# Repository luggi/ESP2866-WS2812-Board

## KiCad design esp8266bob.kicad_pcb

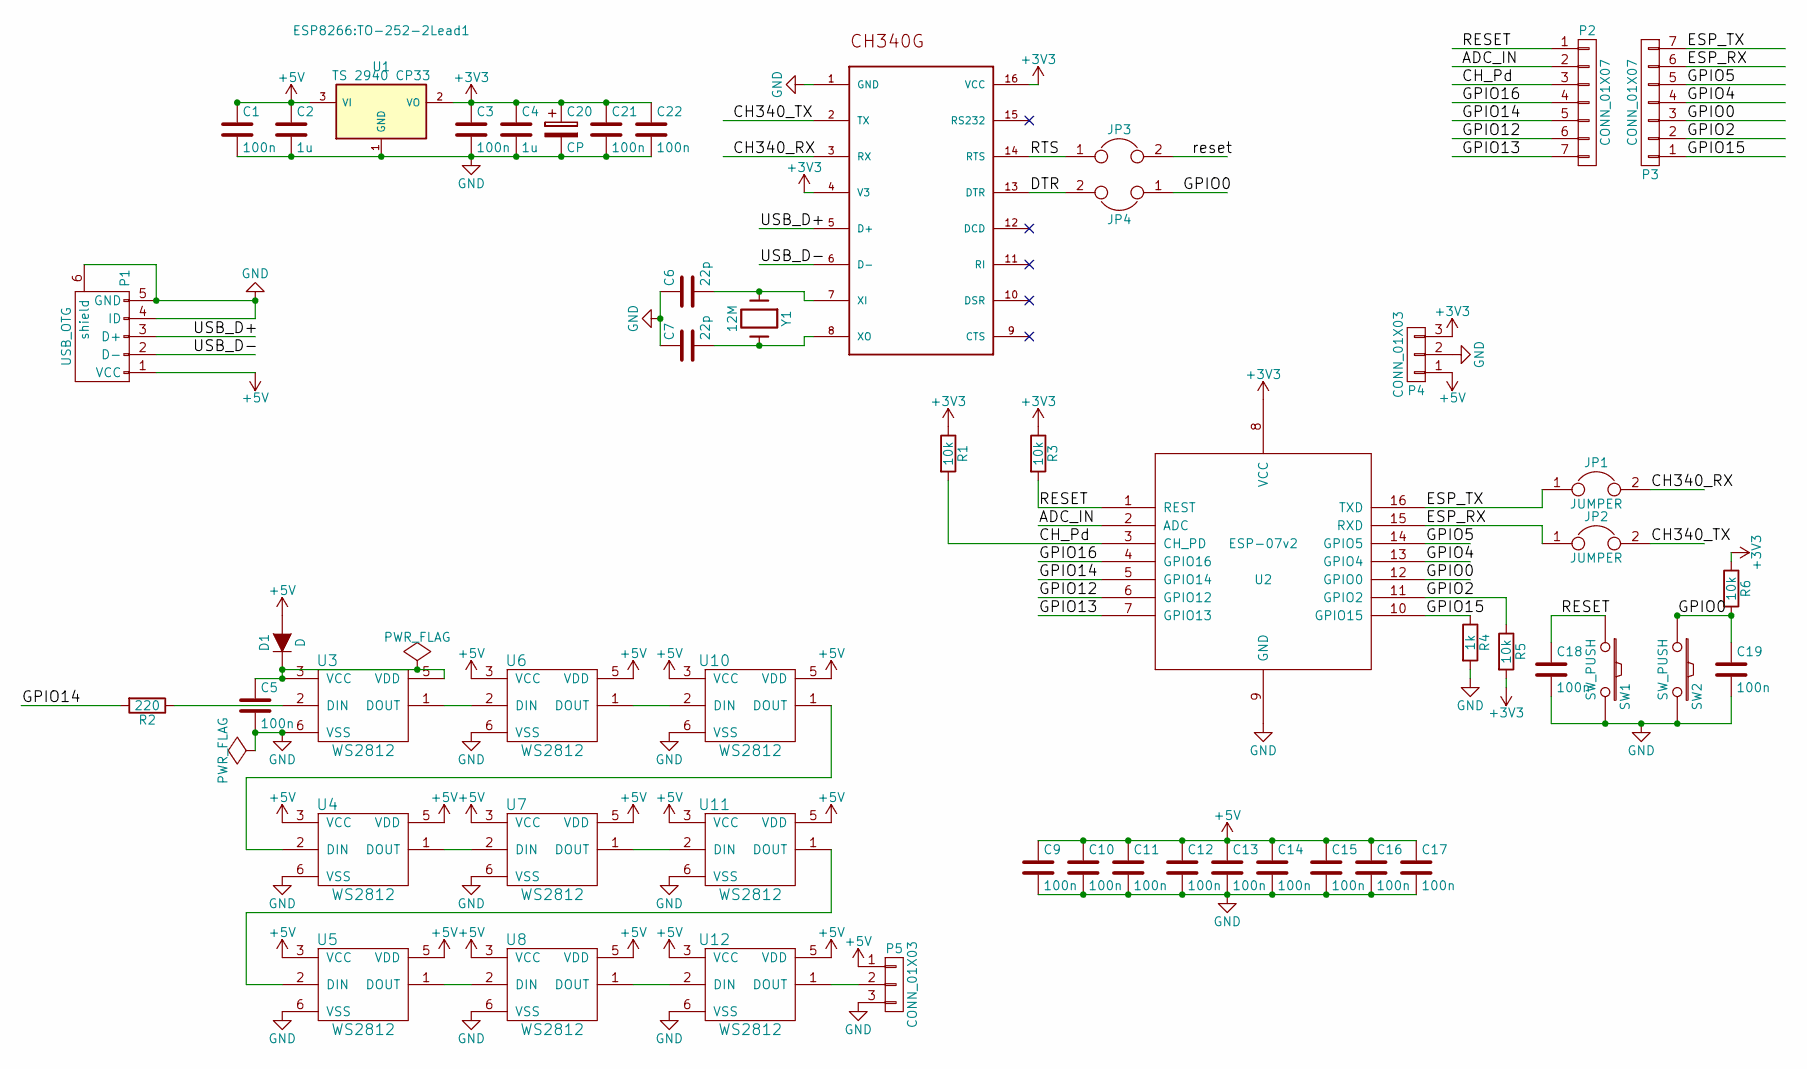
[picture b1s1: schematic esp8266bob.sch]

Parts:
C1, C3, C5, C9, C10, C11, C12, C13, C14, C15, C16, C17, C18, C19, C21, C22: 100n; C_0603_HandSoldering
C2, C4: 1u; C_0603_HandSoldering
C6, C7: 22p; C_0603_HandSoldering
C20: CP; c_elec_6.3x5.8
D1: D; MiniMELF_Handsoldering
JP1, JP2, JP3, JP4: JUMPER; S_JUMPER_2
P1: USB_OTG; USB_Micro-B
P2, P3: CONN_01X07; Pin_Header_Straight_1x07
P4, P5: CONN_01X03; Pin_Header_Straight_1x03
R1, R3, R5, R6: 10k; R_0603_HandSoldering
R2: 220; R_0603_HandSoldering
R4: 1k; R_0603_HandSoldering
SW1, SW2: SW_PUSH; SW_SPST_KMR2
U1: TS 2940 CP33; TO-252-2Lead1
U2: ESP-07v2
U3, U4, U5, U6, U7, U8, U10, U11, U12: WS2812; 5050smd
U9: CH340G; SOP-16
Y1: 12M; Crystal_HC49-U_Vertical

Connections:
+3V3: C3.1, C4.1, C20.1, C21.1, C22.1, P4.3, R1.1, R3.1, R5.2, R6.1, U1.2 (VO), U2.8 (VCC), U9.4 (V3), U9.16 (VCC)
+5V: C1.1, C2.1, C9.1, C10.1, C11.1, C12.1, C13.1, C14.1, C15.1, C16.1, C17.1, D1.2 (A), P1.1 (VCC), P4.1, P5.1, U1.3 (VI), U4.3 (VCC), U4.5 (VDD), U5.3 (VCC), U5.5 (VDD), U6.3 (VCC), U6.5 (VDD), U7.3 (VCC), U7.5 (VDD), U8.3 (VCC), U8.5 (VDD), U10.3 (VCC), U10.5 (VDD), U11.3 (VCC), U11.5 (VDD), U12.3 (VCC), U12.5 (VDD)
/ADC_IN: P2.2, U2.2 (ADC)
/CH340_RX: JP1.2, U9.3 (RX)
/CH340_TX: JP2.2, U9.2 (TX)
/CH_Pd: P2.3, R1.2, U2.3 (CH_PD)
/DTR: JP4.2, U9.13 (DTR)
/ESP_RX: JP2.1, P3.6, U2.15 (RXD)
/ESP_TX: JP1.1, P3.7, U2.16 (TXD)
/GPIO0: C19.1, JP4.1, P3.3, R6.2, SW2.1, U2.12 (GPIO0); also elsewhere on the board
/GPIO2: P3.2, R5.1, U2.11 (GPIO2)
/GPIO4: P3.4, U2.13 (GPIO4)
/GPIO5: P3.5, U2.14 (GPIO5)
/GPIO12: P2.6, U2.6 (GPIO12)
/GPIO13: P2.7, U2.7 (GPIO13)
/GPIO14: P2.5, R2.2, U2.5 (GPIO14)
/GPIO15: P3.1, R4.1, U2.10 (GPIO15)
/GPIO16: P2.4, U2.4 (GPIO16)
/RESET: C18.1, JP3.2, P2.1, R3.2, SW1.1, U2.1 (REST); also elsewhere on the board
/RTS: JP3.1, U9.14 (RTS)
/USB_D+: P1.3 (D+), U9.5 (D+)
/USB_D-: P1.2 (D-), U9.6 (D-)
GND: C1.2, C2.2, C3.2, C4.2, C5.2, C6.1, C7.1, C9.2, C10.2, C11.2, C12.2, C13.2, C14.2, C15.2, C16.2, C17.2, C18.2, C19.2, C20.2, C21.2, C22.2, P1.4 (ID), P1.5 (GND), P1.6 (shield), P4.2, P5.3, R4.2, SW1.2, SW2.2, U1.1 (GND), U2.9 (GND), U3.6 (VSS), U4.6 (VSS), U5.6 (VSS), U6.6 (VSS), U7.6 (VSS), U8.6 (VSS), U9.1 (GND), U10.6 (VSS), U11.6 (VSS), U12.6 (VSS); also elsewhere on the board
unnamed: C5.1, D1.1 (K), U3.3 (VCC), U3.5 (VDD)
unnamed: C6.2, U9.7 (XI), Y1.1
unnamed: C7.2, U9.8 (XO), Y1.2
unnamed: P5.2, U12.1 (DOUT)
unnamed: R2.1, U3.2 (DIN)
unnamed: U3.1 (DOUT), U6.2 (DIN)
unnamed: U4.1 (DOUT), U7.2 (DIN)
unnamed: U5.1 (DOUT), U8.2 (DIN)
unnamed: U4.2 (DIN), U10.1 (DOUT)
unnamed: U6.1 (DOUT), U10.2 (DIN)
unnamed: U5.2 (DIN), U11.1 (DOUT)
unnamed: U7.1 (DOUT), U11.2 (DIN)
unnamed: U8.1 (DOUT), U12.2 (DIN)

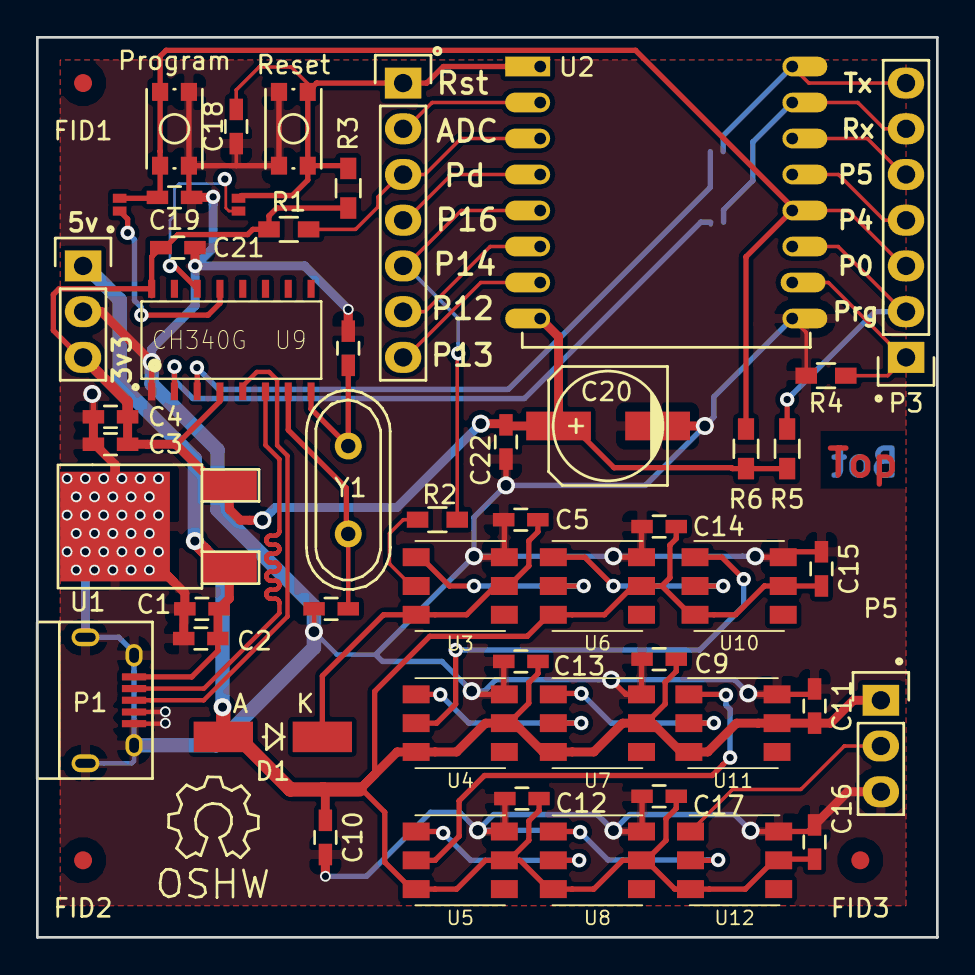
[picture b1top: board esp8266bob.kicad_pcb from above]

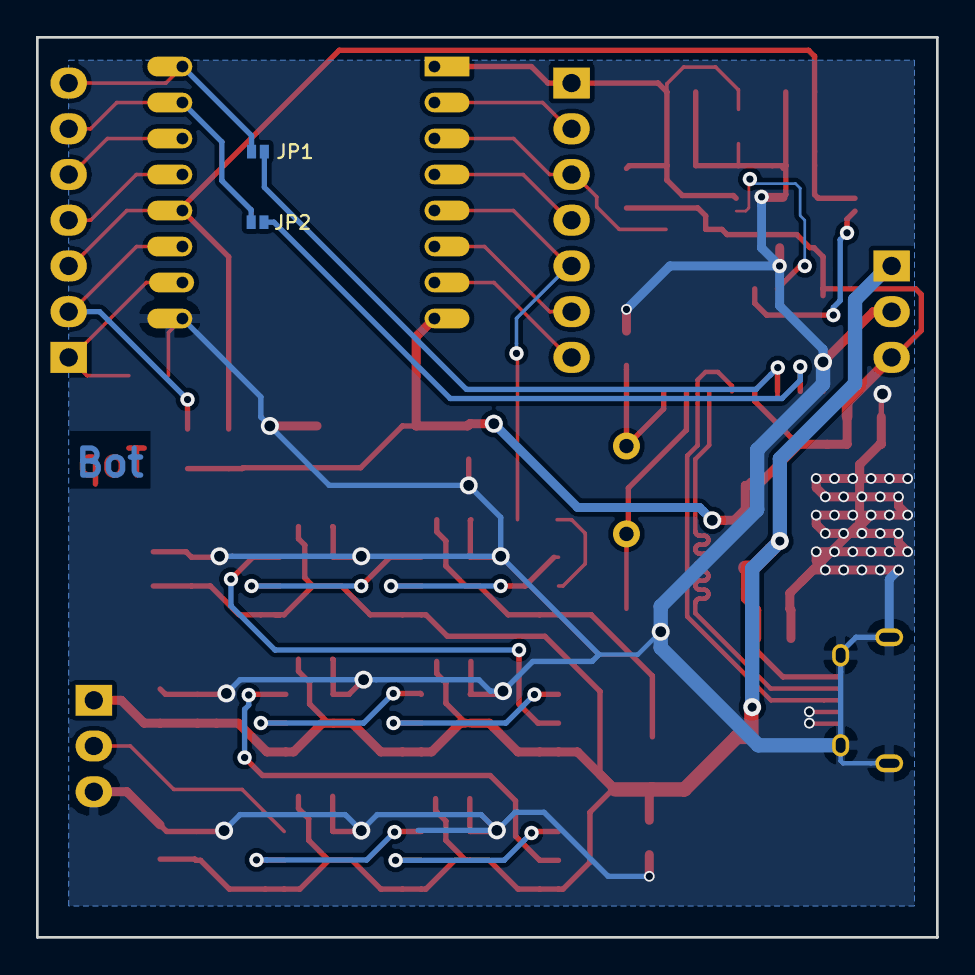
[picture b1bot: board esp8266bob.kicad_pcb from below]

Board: 2 copper layers, 50.0 x 50.0 mm, 55 parts (2 on the bottom side), 36 nets.

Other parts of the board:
FID1, FID2, FID3: Fiducial_1mm_Dia_2.54mm_Outer_CopperTop
Program: SW_PUSH; SW_SPST_KMR2
Reset: SW_PUSH; SW_SPST_KMR2

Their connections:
/GPIO0: Program.1; also elsewhere on the board
/RESET: Reset.1; also elsewhere on the board
GND: Program.2, Reset.2; also elsewhere on the board

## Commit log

2016-03-22 initial design
2016-03-22 libs added
2016-03-22 PCB!!!
2016-03-22 gerber generated
2016-03-22 finalize
2016-04-11 bugs fixed in the schematic
2016-04-16 bugfixes, auto programming pins connected
